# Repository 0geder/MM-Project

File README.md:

# 🐭 Micro-mouse Project – Power Subsystem (Group 14)

This repository contains the complete hardware design, testing documentation, and supporting files for the **Power Subsystem** developed by **Group 14** as part of the University of Cape Town’s **EEE3088F Micro-mouse Project**.

The Power Subsystem forms the heart of the Micro-mouse robot, supplying regulated 3.3V and 5V rails, enabling safe LiPo battery charging, driving DC motors, and interfacing cleanly with the Processor and Motherboard modules.

---

## ⚡ System Overview

- **Input Power Sources**: 
  - LiPo Battery (3.7V nominal)
  - USB-C PD input (5V or 9V via CH224K)
- **Outputs**:
  - 3.3V rail (max 300mA)
  - 5V rail (max 1.5A)
  - Bidirectional control of four DC motors via dual H-bridge ICs
  - Battery voltage and current monitoring (INA219 over I2C)
- **Key Features**:
  - Ultra-low standby current mode (<30µA)
  - Manual ON/OFF control (SW2)
  - High-side load switching for external peripherals
  - Compact PCB (82mm x 60mm) with 2x16-pin interface

---

## 📁 Repository Structure
- `/hardware/kicad/` – Full KiCad project files (`.kicad_pro`, `.kicad_sch`, `.kicad_pcb`, etc.)
- `/hardware/production_files/` – Gerbers, BOM, CPL files for JLCPCB submission

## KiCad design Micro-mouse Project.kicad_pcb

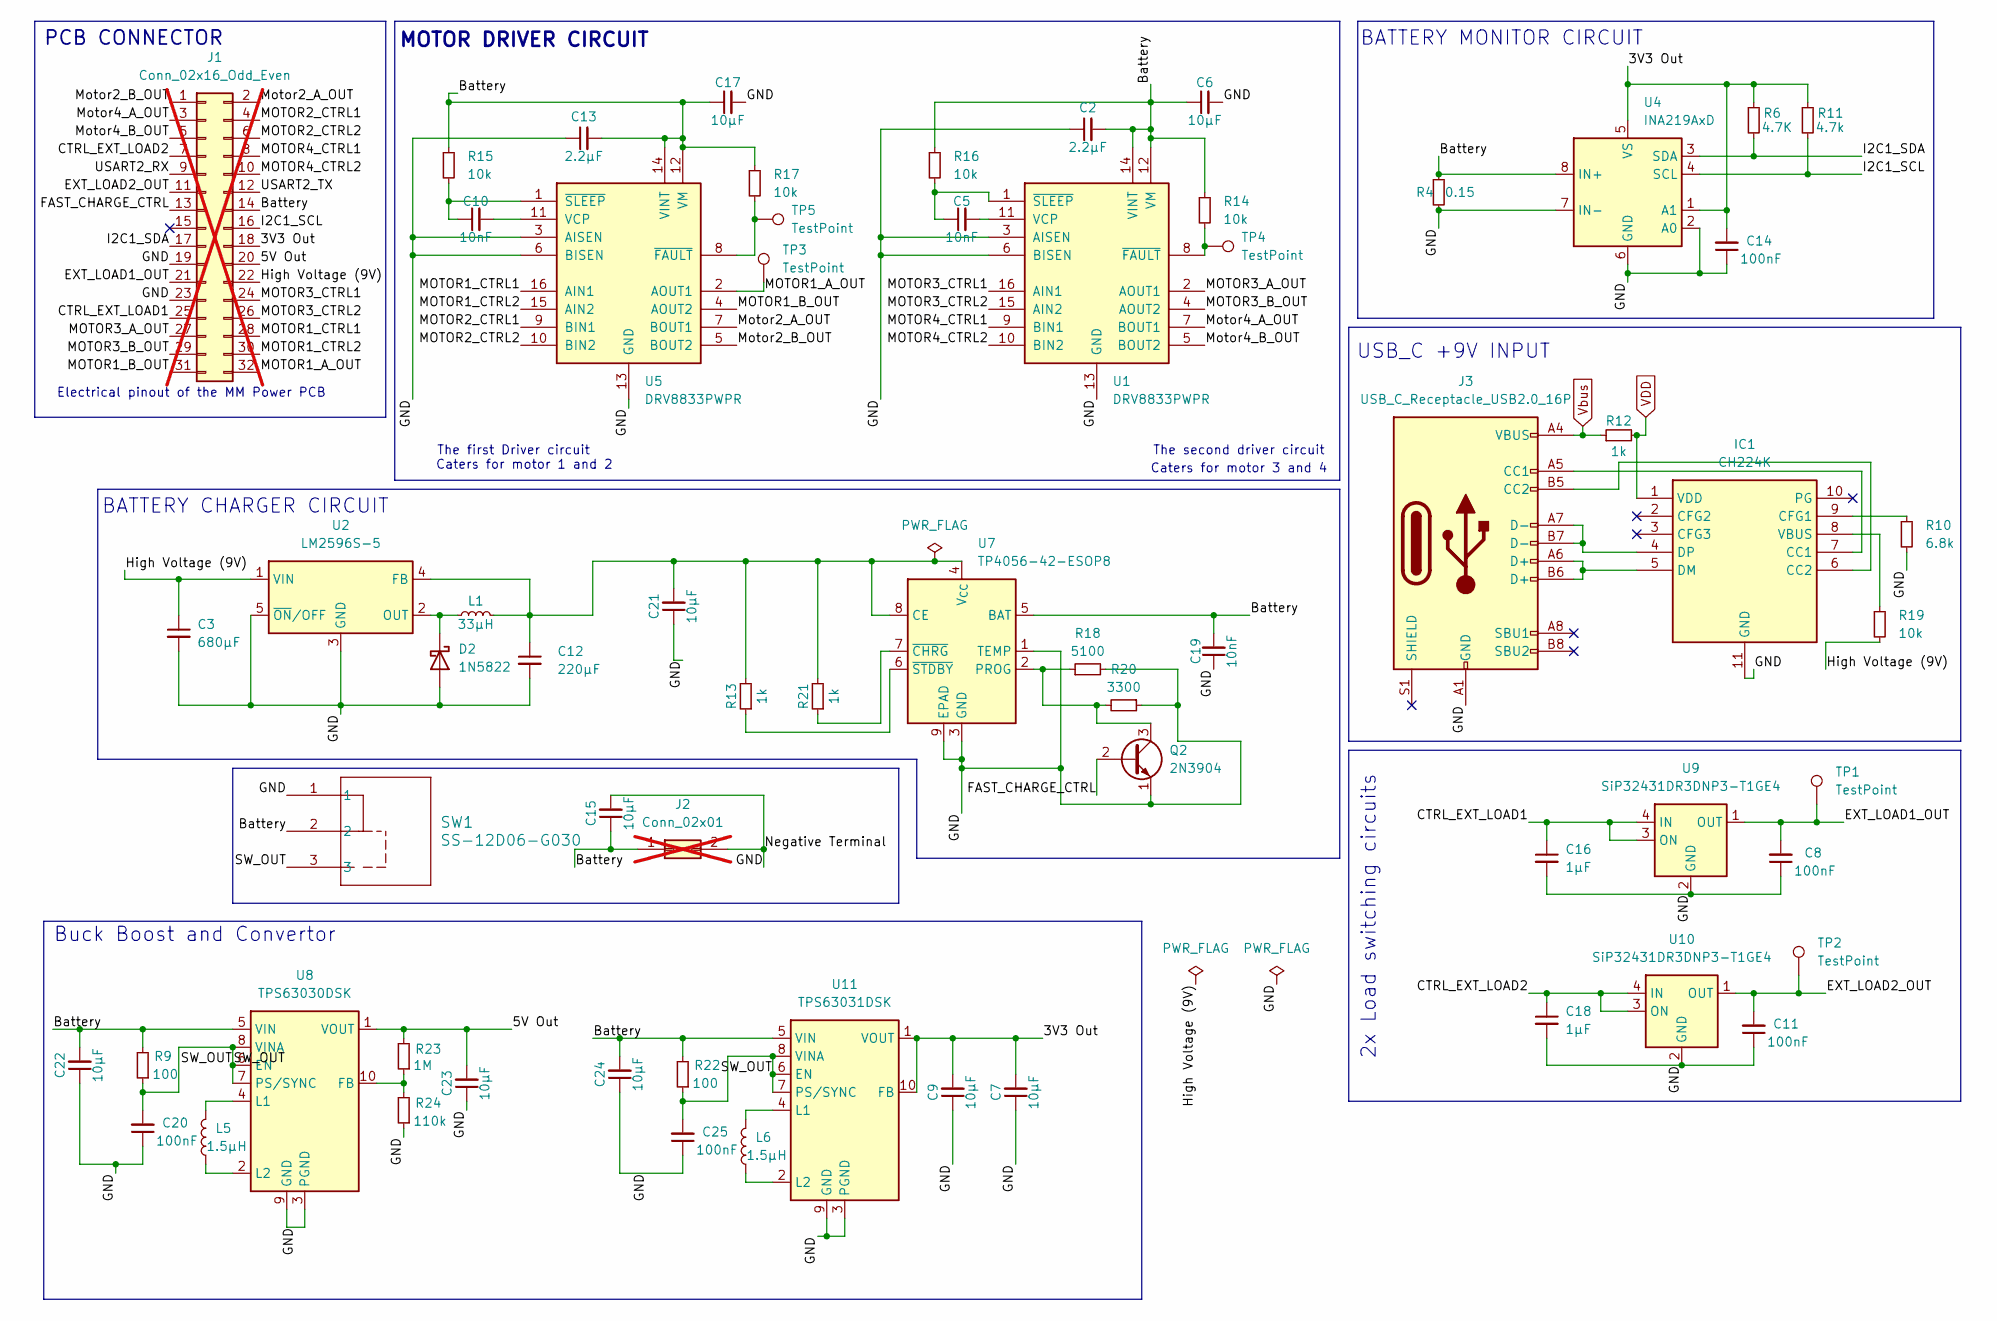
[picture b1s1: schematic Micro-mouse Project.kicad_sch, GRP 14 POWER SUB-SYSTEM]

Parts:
C2, C13: 2.2μF; C_0402_1005Metric_Pad0.74x0.62mm_HandSolder; LCSC C12530
C3: 680μF; C_Radial_D10.0mm_H20.0mm_P5.00mm; LCSC C23777
C5, C10, C19: 10nF; C_0805_2012Metric_Pad1.18x1.45mm_HandSolder; LCSC C1710
C6, C7, C9, C15, C17, C21, C22, C23, C24: 10μF; C_1206_3216Metric_Pad1.33x1.80mm_HandSolder; LCSC C13585
C8, C11, C14, C20, C25: 100nF; C_0402_1005Metric_Pad0.74x0.62mm_HandSolder; LCSC C1525
C12: 220μF; C_1206_3216Metric_Pad1.33x1.80mm_HandSolder
C16, C18: 1μF; C_1206_3216Metric_Pad1.33x1.80mm_HandSolder; LCSC C1848
D2: 1N5822; DIO_SS34; LCSC C8678
IC1: CH224K; SOP100P600X180-11N; Manufacturer_Part_Number CH224K
J1: Conn_02x16_Odd_Even; not fitted
J2: Conn_02x01; not fitted
J3: USB_C_Receptacle_USB2.0_16P; USB_C_Receptacle_GCT_USB4105-xx-A_16P_TopMnt_Horizontal; LCSC C393939
L1: 33μH; L_12x12mm_H4.5mm
L5, L6: 1.5µH; L_1206_3216Metric_Pad1.22x1.90mm_HandSolder; LCSC C74477
Q2: 2N3904; SOT-23; LCSC C18536
R4: 0.15; R_1206_3216Metric_Pad1.30x1.75mm_HandSolder; LCSC C149670
R6: 4.7K; R_0603_1608Metric_Pad0.98x0.95mm_HandSolder; LCSC C23162
R9, R22: 100; R_0805_2012Metric_Pad1.20x1.40mm_HandSolder; LCSC C17408
R10: 6.8k; R_0603_1608Metric_Pad0.98x0.95mm_HandSolder; LCSC C23212
R11: 4.7k; R_0603_1608Metric_Pad0.98x0.95mm_HandSolder; LCSC C23162
R12, R13, R21: 1k; R_1206_3216Metric_Pad1.30x1.75mm_HandSolder; LCSC C4410
R14, R15, R16, R17, R19: 10k; R_0805_2012Metric_Pad1.20x1.40mm_HandSolder; LCSC C17414
R18: 5100; R_0603_1608Metric; LCSC C23186
R20: 3300; R_0603_1608Metric; LCSC C22978
R23: 1M; R_1206_3216Metric_Pad1.30x1.75mm_HandSolder; LCSC C17927
R24: 110k; R_0805_2012Metric_Pad1.20x1.40mm_HandSolder; LCSC C17422
SW1: SS-12D06-G030; SS-12D06_GSW; LCSC C17179519
TP1, TP2, TP3, TP4, TP5: TestPoint; TestPoint_Pad_D2.0mm
U1, U5: DRV8833PWPR; IC_DRV8833PWPR; LCSC C50506
U2: LM2596S-5; TO-263-5_TabPin3; LCSC C10002
U4: INA219AxD; SOT65P280X145-8N; LCSC C87469
U7: TP4056-42-ESOP8; SOIC127P600X175-9N; LCSC C16581
U8: TPS63030DSK; WSON-10-1EP_2.5x2.5mm_P0.5mm_EP1.2x2mm; LCSC C12462
U9: SiP32431DR3DNP3-T1GE4; SOT-363_SC-70-6; LCSC C727398
U10: SiP32431DR3DNP3-T1GE4; SON50P120X160X60-5N; LCSC C727398
U11: TPS63031DSK; WSON-10-1EP_2.5x2.5mm_P0.5mm_EP1.2x2mm; LCSC C12462

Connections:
/3V3 Out: C7.2, C9.2, C14.2, J1.18, R6.1, R11.1, U4.1 (A1), U4.5 (VS), U11.1 (VOUT), U11.10 (FB)
/5V Out: C23.2, J1.20, R23.2, U8.1 (VOUT)
/Battery: C2.2, C6.1, C13.2, C15.1, C17.1, C19.2, C22.2, C24.2, J1.14, J2.1, R4.1, R9.2, R14.1, R15.1, R16.1, R17.1, R22.2, SW1.2, U1.12 (VM), U1.14 (VINT), U4.8 (IN+), U5.12 (VM), U5.14 (VINT), U7.5 (BAT), U8.5 (VIN), U11.5 (VIN)
/CTRL_EXT_LOAD1: C16.1, J1.25, U9.3 (ON), U9.4 (IN)
/CTRL_EXT_LOAD2: C18.1, J1.7, U10.3 (ON), U10.4 (IN)
/EXT_LOAD1_OUT: C8.2, J1.21, TP1.1, U9.1 (OUT)
/EXT_LOAD2_OUT: C11.2, J1.11, TP2.1, U10.1 (OUT)
/FAST_CHARGE_CTRL: J1.13, Q2.2 (B)
/GND: C2.1, C3.2, C6.2, C7.1, C8.1, C9.1, C11.1, C12.2, C13.1, C14.1, C15.2, C16.2, C17.2, C18.2, C19.1, C20.1, C21.1, C22.1, C23.1, C24.1, C25.1, D2.2 (A), IC1.11 (GND), J1.19, J1.23, J2.2, J3.A1 (GND), J3.A12 (GND), J3.B1 (GND), J3.B12 (GND), Q2.1 (E), R4.2, R10.2, R18.2, R20.1, R24.1, SW1.1, U1.3 (AISEN), U1.6 (BISEN), U1.13 (GND), U1.17 (GND), U2.3 (GND), U2.5 (~ON/OFF), U4.2 (A0), U4.6 (GND), U4.7 (IN-), U5.3 (AISEN), U5.6 (BISEN), U5.13 (GND), U5.17 (GND), U7.1 (TEMP), U7.3 (GND), U7.9 (EPAD), U8.3 (PGND), U8.9 (GND), U8.11 (PGND), U9.2 (GND), U9.5 (GND), U10.2 (GND), U10.5 (GND), U11.3 (PGND), U11.9 (GND), U11.11 (PGND)
/High Voltage (9V): C3.1, J1.22, R19.2, U2.1 (VIN)
/I2C1_SCL: J1.16, R11.2, U4.4 (SCL)
/I2C1_SDA: J1.17, R6.2, U4.3 (SDA)
/MOTOR1_A_OUT: J1.32, TP3.1, U5.2 (AOUT1)
/MOTOR1_B_OUT: J1.31, U5.4 (AOUT2)
/MOTOR1_CTRL1: J1.28, U5.16 (AIN1)
/MOTOR1_CTRL2: J1.30, U5.15 (AIN2)
/MOTOR2_CTRL1: J1.4, U5.9 (BIN1)
/MOTOR2_CTRL2: J1.6, U5.10 (BIN2)
/MOTOR3_A_OUT: J1.27, U1.2 (AOUT1)
/MOTOR3_B_OUT: J1.29, U1.4 (AOUT2)
/MOTOR3_CTRL1: J1.24, U1.16 (AIN1)
/MOTOR3_CTRL2: J1.26, U1.15 (AIN2)
/MOTOR4_CTRL1: J1.8, U1.9 (BIN1)
/MOTOR4_CTRL2: J1.10, U1.10 (BIN2)
/Motor2_A_OUT: J1.2, U5.7 (BOUT1)
/Motor2_B_OUT: J1.1, U5.5 (BOUT2)
/Motor4_A_OUT: J1.3, U1.7 (BOUT1)
/Motor4_B_OUT: J1.5, U1.5 (BOUT2)
/SW_OUT: C20.2, C25.2, R9.1, R22.1, SW1.3, U8.6 (EN), U8.7 (PS/SYNC), U8.8 (VINA), U11.6 (EN), U11.7 (PS/SYNC), U11.8 (VINA)
/USART2_RX: J1.9
/USART2_TX: J1.12
unnamed: D2.1 (K), L1.1, U2.2 (OUT)
unnamed: IC1.7 (CC1), J3.A5 (CC1)
unnamed: IC1.6 (CC2), J3.B5 (CC2)
unnamed: IC1.9 (CFG1), R10.1
unnamed: IC1.5 (DM), J3.A6 (D+), J3.B6 (D+)
unnamed: IC1.4 (DP), J3.A7 (D-), J3.B7 (D-)
unnamed: IC1.8 (VBUS), R19.1
unnamed: Q2.3 (C), R18.1, R20.2, U7.2 (PROG)
unnamed: C5.2, U1.11 (VCP)
unnamed: R14.2, TP4.1, U1.8 (~FAULT)
unnamed: C5.1, R16.2, U1.1 (~SLEEP)
unnamed: C12.1, C21.2, L1.2, R13.2, R21.2, U2.4 (FB), U7.4 (V_{CC}), U7.8 (CE)
unnamed: C10.2, U5.11 (VCP)
unnamed: R17.2, TP5.1, U5.8 (~FAULT)
unnamed: C10.1, R15.2, U5.1 (~SLEEP)
unnamed: R21.1, U7.7 (~CHRG)
unnamed: R13.1, U7.6 (~STDBY)
unnamed: R23.1, R24.2, U8.10 (FB)
unnamed: L5.2, U8.4 (L1)
unnamed: L5.1, U8.2 (L2)
unnamed: L6.2, U11.4 (L1)
unnamed: L6.1, U11.2 (L2)
VDD: IC1.1 (VDD), R12.2
Vbus: J3.A4 (VBUS), J3.A9 (VBUS), J3.B4 (VBUS), J3.B9 (VBUS), R12.1

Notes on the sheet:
BATTERY MONITOR CIRCUIT
BATTERY CHARGER CIRCUIT
The first Driver circuit
Buck Boost and Convertor
MOTOR DRIVER CIRCUIT
The second driver circuit
2x Load switching circuits
Caters for motor 3 and 4
PCB CONNECTOR
Caters for motor 1 and 2
Electrical pinout of the MM Power PCB
USB_C +9V INPUT

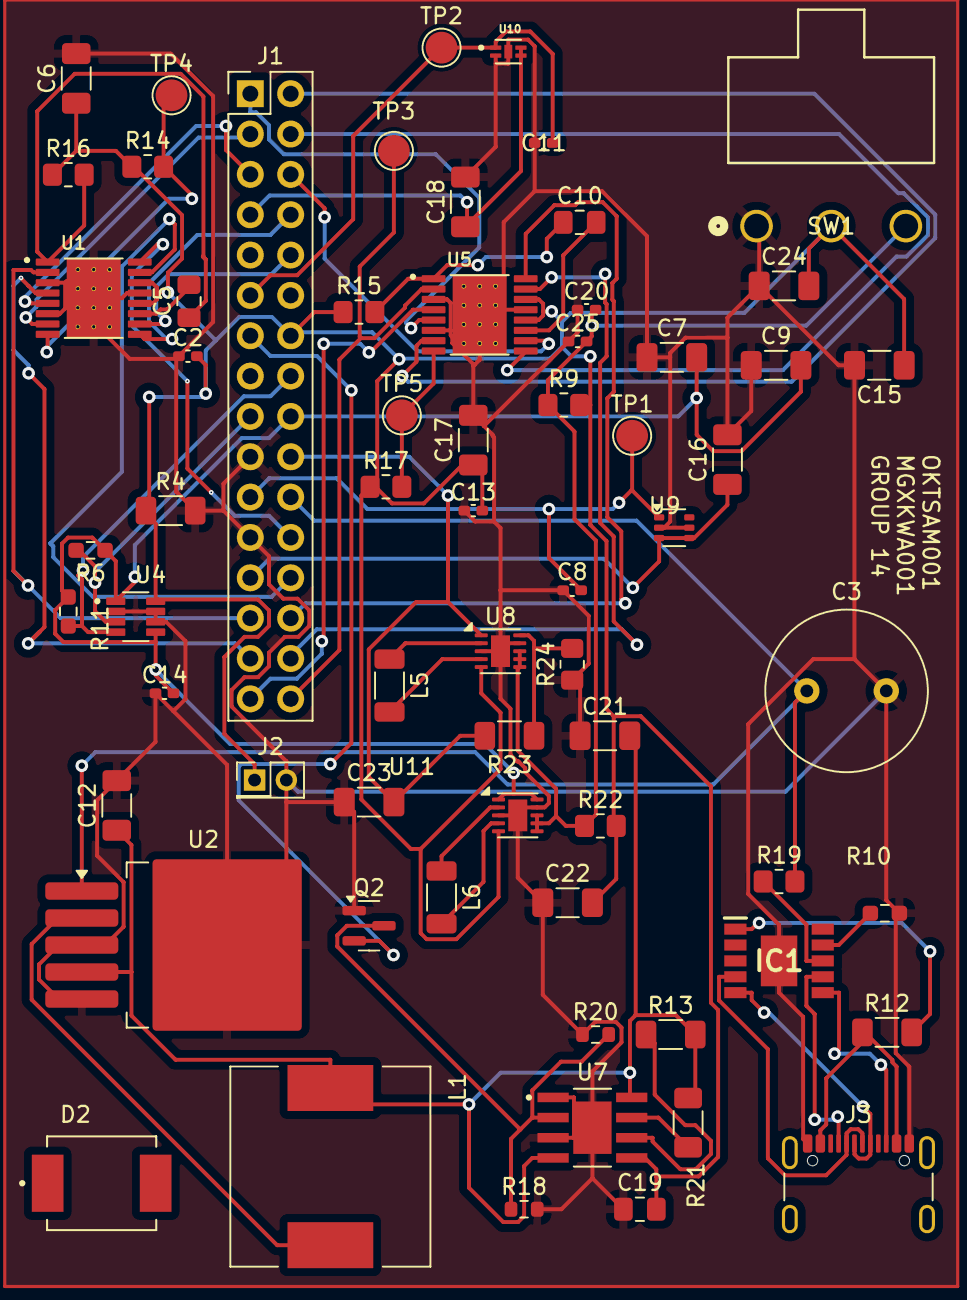
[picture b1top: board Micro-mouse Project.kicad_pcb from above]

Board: 2 copper layers, 65 parts (0 on the bottom side), 53 nets.

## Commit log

2025-03-25 Initial commit of KiCad project files
2025-04-24 The Motor Management Circuit
    This caters for the motor and the switching ON/OFF of the power subsystem.
2025-04-24 Complete Motor Management
    Made sure all power flags are included.
2025-04-24 Revert "Complete Motor Management"
2025-04-24 Full Schematic
    Final draft
2025-04-24 Complete Micro Mouse Power Subsystem Design
    Files containing the completed design of the Micro-mouse project plus the PCB design.
